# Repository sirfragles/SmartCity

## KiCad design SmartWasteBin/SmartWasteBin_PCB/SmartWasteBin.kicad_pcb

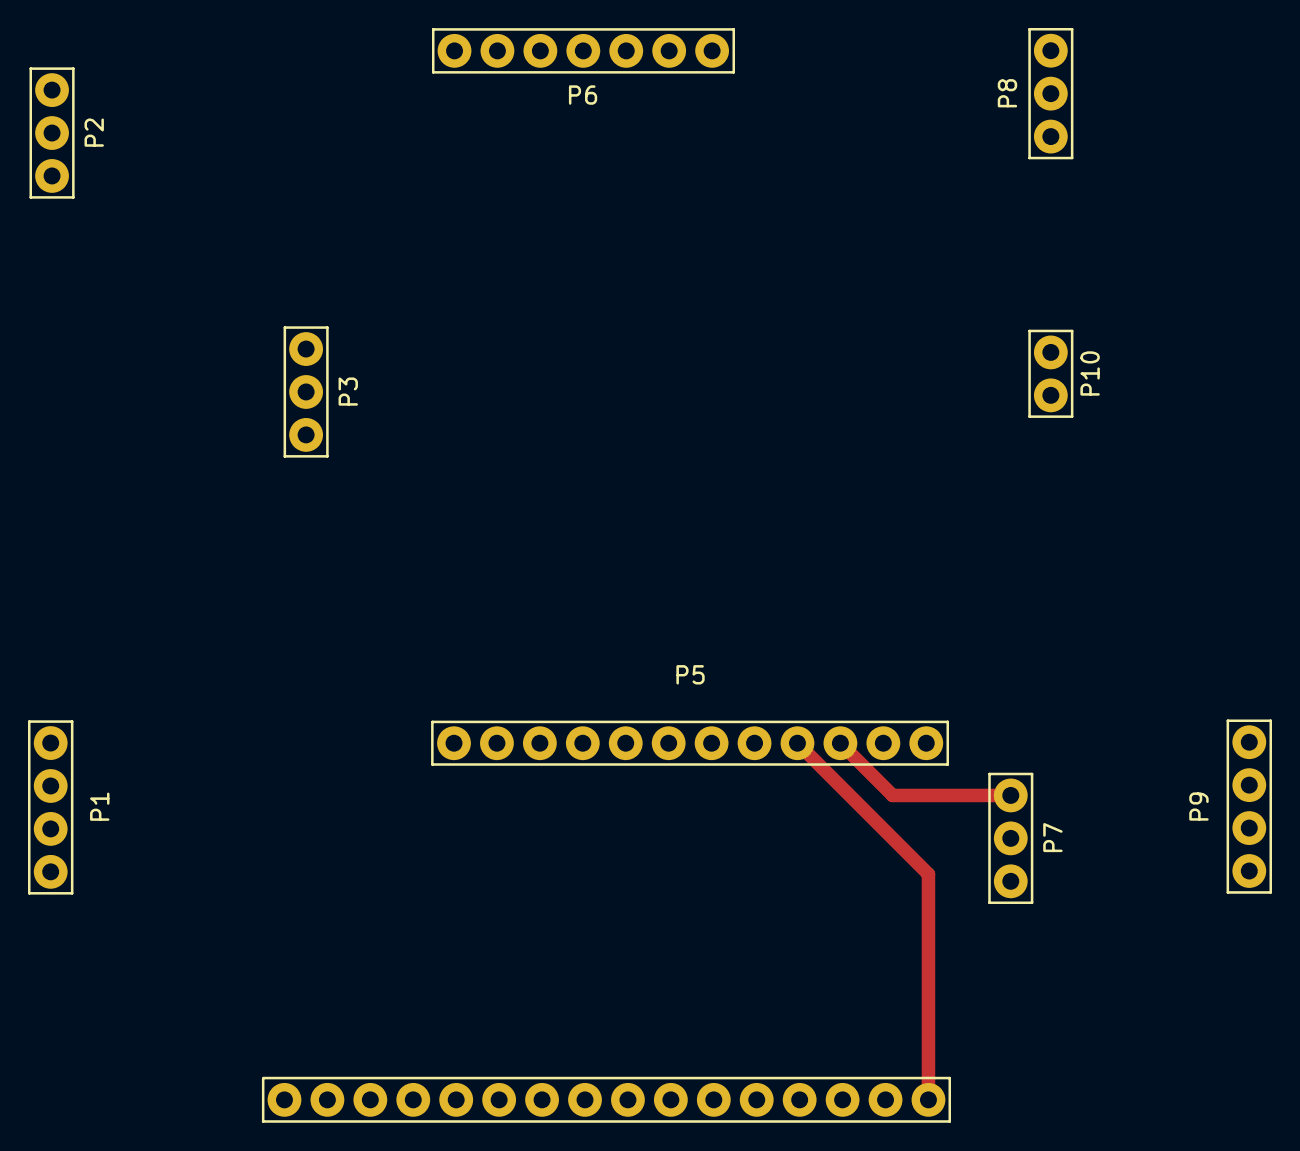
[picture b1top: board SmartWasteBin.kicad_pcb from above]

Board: 2 copper layers, 10 parts (0 on the bottom side), 18 nets.

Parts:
P1, P9: CONN_01X04; CONN_01x04
P2, P3, P7, P8: CONN_01X03; CONN_01x03
P4: CONN_01X16; CONN_01x16
P5: CONN_01X12; CONN_01x12
P6: CONN_01X07; CONN_01x07
P10: CONN_01X02; CONN_01x02

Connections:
unnamed: P1.1, P9.1, P10.2
unnamed: P1.2, P5.7
unnamed: P1.3, P5.6
unnamed: P1.4, P9.4, P10.1
unnamed: P2.1, P4.4, P6.1, P8.1
unnamed: P2.2, P3.3, P4.2, P6.2, P8.2
unnamed: P2.3, P5.5
unnamed: P3.1, P5.8
unnamed: P4.5, P8.3
unnamed: P4.11, P9.3
unnamed: P4.12, P9.2
unnamed: P4.13, P6.7
unnamed: P4.14, P6.6
unnamed: P4.15, P6.5
unnamed: P4.16, P5.4
unnamed: P5.1, P6.4
unnamed: P5.2, P6.3
unnamed: P5.3, P7.3

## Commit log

2018-12-07 Upload
2018-12-07 Update PCB
